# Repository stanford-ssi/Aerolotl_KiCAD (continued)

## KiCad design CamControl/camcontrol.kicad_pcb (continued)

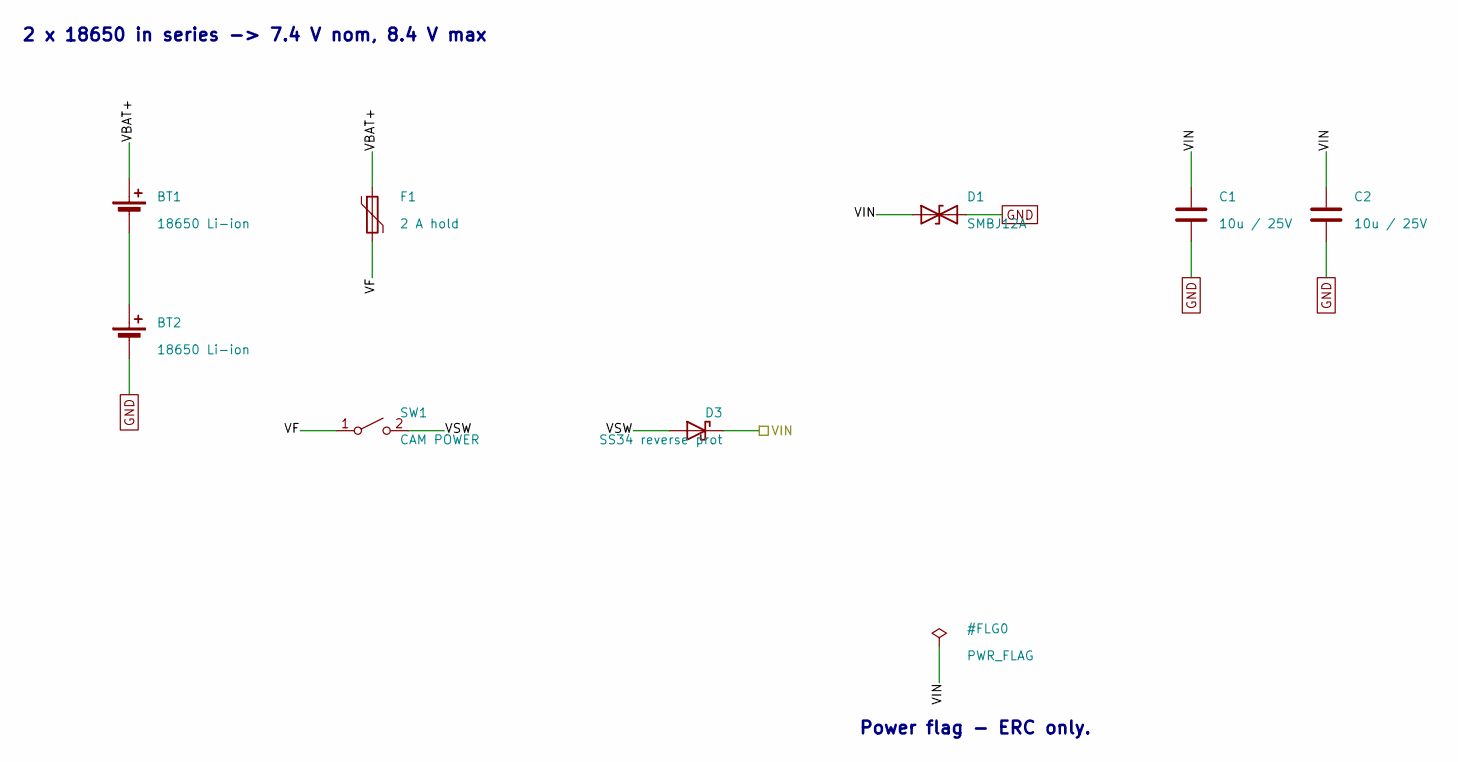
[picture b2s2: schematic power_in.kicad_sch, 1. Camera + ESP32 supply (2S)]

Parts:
BT1, BT2: 18650 Li-ion; BatteryHolder_Keystone_1042_1x18650; MPN 1042
C1, C2: 10u / 25V; C_0805_2012Metric; MPN CL21A106KAYNNNE
D1: SMBJ12A; D_SMB; MPN SMBJ12A
D3: SS34 reverse prot; D_SMB; MPN B340B-13-F
F1: 2 A hold; Fuse_1812_4532Metric; MPN 1812L200/12DR
SW1: CAM POWER; Molex_Micro-Fit_3.0_43650-0215_1x02_P3.00mm_Vertical; MPN 0436500215

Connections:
/1. Battery 2S + protection/VBAT+: BT1.1 (+), F1.1
/1. Battery 2S + protection/VF: F1.2, SW1.1 (A)
/1. Battery 2S + protection/VIN: C1.1, C2.1, D1.1 (A1), D3.1 (K); also elsewhere on the board
/1. Battery 2S + protection/VSW: D3.2 (A), SW1.2 (B)
GND: BT2.2 (-), C1.2, C2.2, D1.2 (A2); also elsewhere on the board
unnamed: BT1.2 (-), BT2.1 (+)

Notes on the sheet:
2 x 18650 in series -> 7.4 V nom, 8.4 V max
Power flag - ERC only.

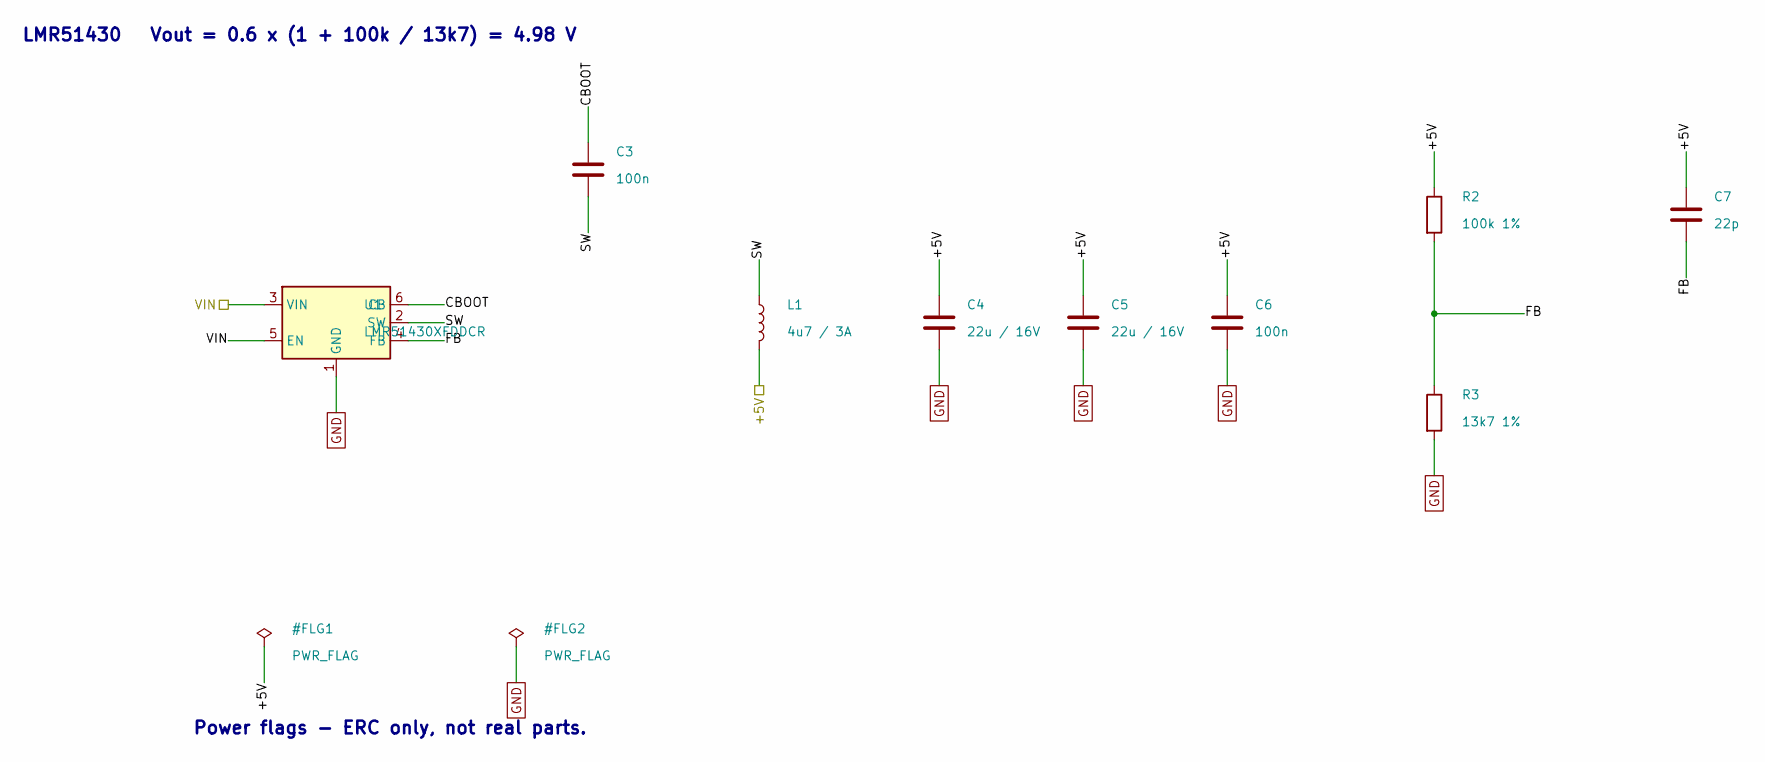
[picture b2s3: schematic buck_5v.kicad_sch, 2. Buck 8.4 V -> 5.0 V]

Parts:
C3, C6: 100n; C_0603_1608Metric; MPN CL10B104KB8NNNC
C4, C5: 22u / 16V; C_0805_2012Metric; MPN CL21A226MOQNNNE
C7: 22p; C_0603_1608Metric; MPN CL10C220JB8NNNC
L1: 4u7 / 3A; L_Bourns_SRN6045TA; MPN SRN6045TA-4R7M
R2: 100k 1%; R_0603_1608Metric; MPN RC0603FR-07100KL
R3: 13k7 1%; R_0603_1608Metric; MPN RC0603FR-0713K7L
U1: LMR51430XFDDCR; SOT-23-6; MPN LMR51430XFDDCR

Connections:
/1. Battery 2S + protection/VIN: U1.3 (VIN), U1.5 (EN); also elsewhere on the board
/2. Buck to 5 V/+5V: C4.1, C5.1, C6.1, C7.1, L1.2, R2.1; also elsewhere on the board
/2. Buck to 5 V/CBOOT: C3.1, U1.6 (CB)
/2. Buck to 5 V/FB: C7.2, R2.2, R3.1, U1.4 (FB)
/2. Buck to 5 V/SW: C3.2, L1.1, U1.2 (SW)
GND: C4.2, C5.2, C6.2, R3.2, U1.1 (GND); also elsewhere on the board

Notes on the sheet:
LMR51430 Vout = 0.6 x (1 + 100k / 13k7) = 4.98 V
Power flags - ERC only, not real parts.

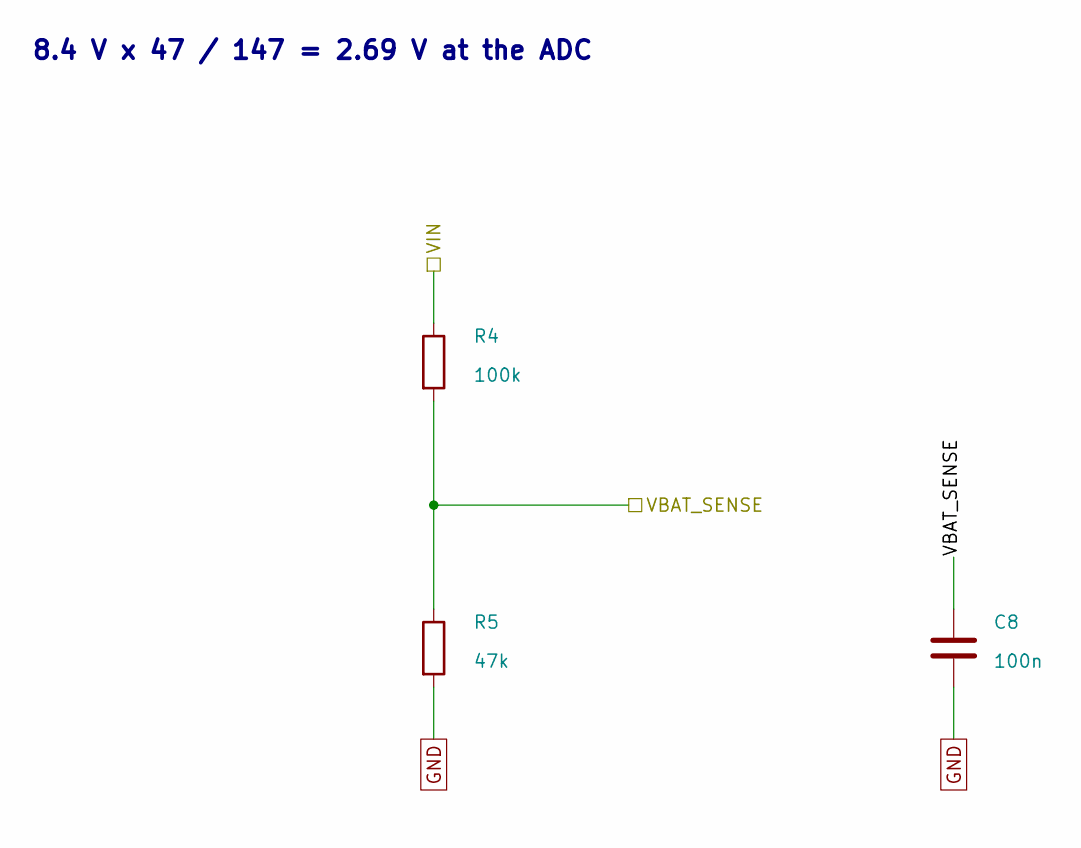
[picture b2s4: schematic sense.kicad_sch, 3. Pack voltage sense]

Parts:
C8: 100n; C_0603_1608Metric; MPN CL10B104KB8NNNC
R4: 100k; R_0603_1608Metric; MPN RC0603FR-07100KL
R5: 47k; R_0603_1608Metric; MPN RC0603FR-0747KL

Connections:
/1. Battery 2S + protection/VIN: R4.1; also elsewhere on the board
/3. Pack voltage sense/VBAT_SENSE: C8.1, R4.2, R5.1; also elsewhere on the board
GND: C8.2, R5.2; also elsewhere on the board

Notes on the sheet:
8.4 V x 47 / 147 = 2.69 V at the ADC

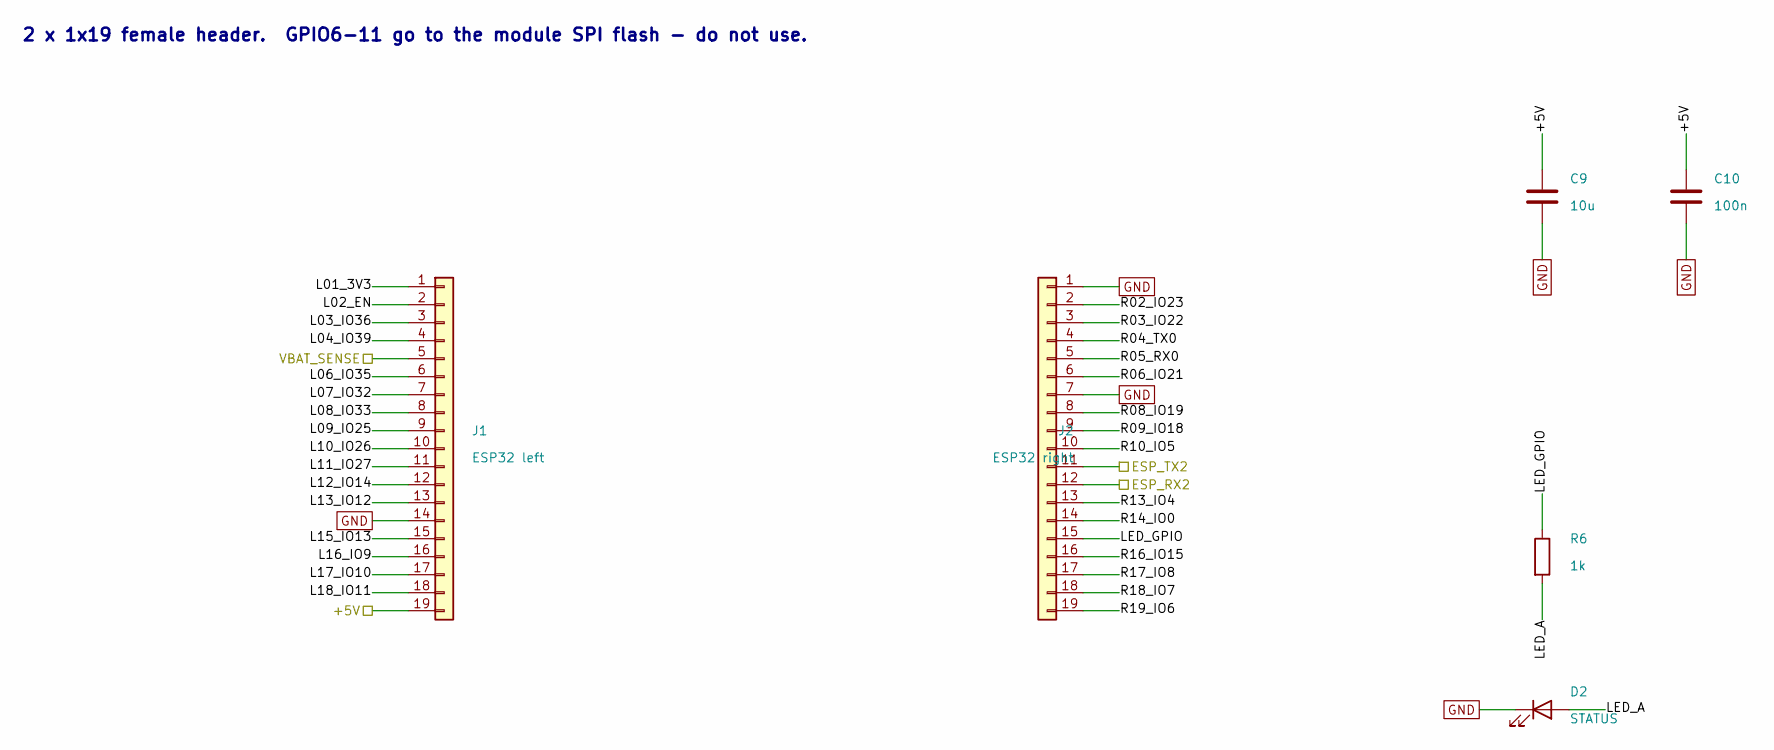
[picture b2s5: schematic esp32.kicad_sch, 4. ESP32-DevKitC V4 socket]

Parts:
C9: 10u; C_0805_2012Metric; MPN CL21A106KAYNNNE
C10: 100n; C_0603_1608Metric; MPN CL10B104KB8NNNC
D2: STATUS; LED_0805_2012Metric; MPN LTST-C171KRKT
J1: ESP32 left; PinSocket_1x19_P2.54mm_Vertical; MPN PPTC191LFBN-RC
J2: ESP32 right; PinSocket_1x19_P2.54mm_Vertical; MPN PPTC191LFBN-RC
R6: 1k; R_0603_1608Metric; MPN RC0603FR-071KL

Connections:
/2. Buck to 5 V/+5V: C9.1, C10.1, J1.19; also elsewhere on the board
/3. Pack voltage sense/VBAT_SENSE: J1.5; also elsewhere on the board
/4. ESP32 socket/ESP_RX2: J2.12; also elsewhere on the board
/4. ESP32 socket/ESP_TX2: J2.11; also elsewhere on the board
/4. ESP32 socket/L01_3V3: J1.1
/4. ESP32 socket/L02_EN: J1.2
/4. ESP32 socket/L03_IO36: J1.3
/4. ESP32 socket/L04_IO39: J1.4
/4. ESP32 socket/L06_IO35: J1.6
/4. ESP32 socket/L07_IO32: J1.7
/4. ESP32 socket/L08_IO33: J1.8
/4. ESP32 socket/L09_IO25: J1.9
/4. ESP32 socket/L10_IO26: J1.10
/4. ESP32 socket/L11_IO27: J1.11
/4. ESP32 socket/L12_IO14: J1.12
/4. ESP32 socket/L13_IO12: J1.13
/4. ESP32 socket/L15_IO13: J1.15
/4. ESP32 socket/L16_IO9: J1.16
/4. ESP32 socket/L17_IO10: J1.17
/4. ESP32 socket/L18_IO11: J1.18
/4. ESP32 socket/LED_A: D2.2 (A), R6.2
/4. ESP32 socket/LED_GPIO: J2.15, R6.1
/4. ESP32 socket/R02_IO23: J2.2
/4. ESP32 socket/R03_IO22: J2.3
/4. ESP32 socket/R04_TX0: J2.4
/4. ESP32 socket/R05_RX0: J2.5
/4. ESP32 socket/R06_IO21: J2.6
/4. ESP32 socket/R08_IO19: J2.8
/4. ESP32 socket/R09_IO18: J2.9
/4. ESP32 socket/R10_IO5: J2.10
/4. ESP32 socket/R13_IO4: J2.13
/4. ESP32 socket/R14_IO0: J2.14
/4. ESP32 socket/R16_IO15: J2.16
/4. ESP32 socket/R17_IO8: J2.17
/4. ESP32 socket/R18_IO7: J2.18
/4. ESP32 socket/R19_IO6: J2.19
GND: C9.2, C10.2, D2.1 (K), J1.14, J2.1, J2.7; also elsewhere on the board

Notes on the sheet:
2 x 1x19 female header. GPIO6-11 go to the module SPI flash - do not use.

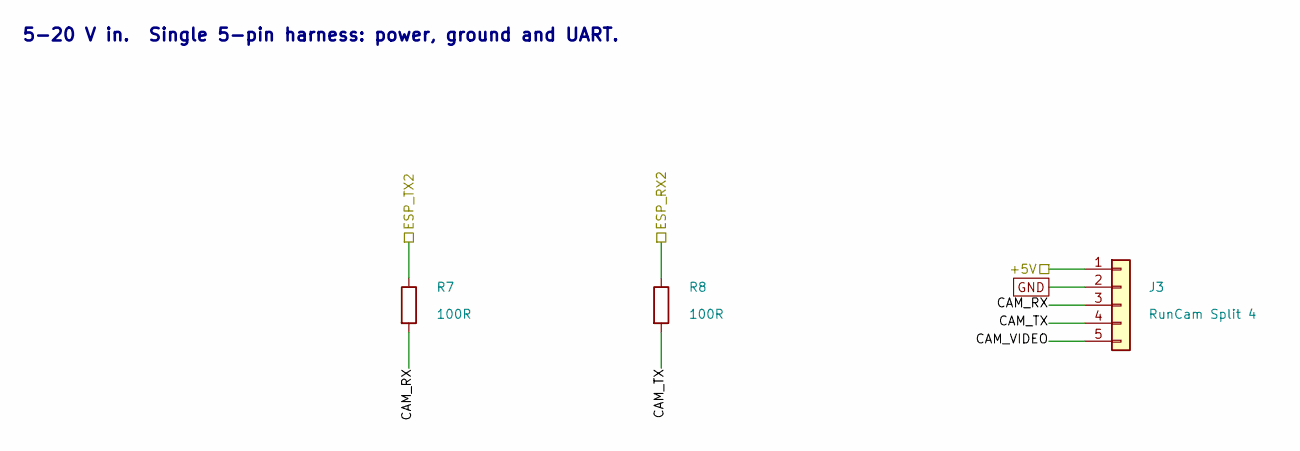
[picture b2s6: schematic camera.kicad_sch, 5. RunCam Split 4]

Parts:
J3: RunCam Split 4; JST_GH_BM05B-GHS-TBT_1x05-1MP_P1.25mm_Vertical; MPN BM05B-GHS-TBT
R7, R8: 100R; R_0603_1608Metric; MPN RC0603FR-07100RL

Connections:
/2. Buck to 5 V/+5V: J3.1; also elsewhere on the board
/4. ESP32 socket/ESP_RX2: R8.1; also elsewhere on the board
/4. ESP32 socket/ESP_TX2: R7.1; also elsewhere on the board
/5. RunCam Split 4/CAM_RX: J3.3, R7.2
/5. RunCam Split 4/CAM_TX: J3.4, R8.2
/5. RunCam Split 4/CAM_VIDEO: J3.5
GND: J3.2; also elsewhere on the board

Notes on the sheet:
5-20 V in. Single 5-pin harness: power, ground and UART.

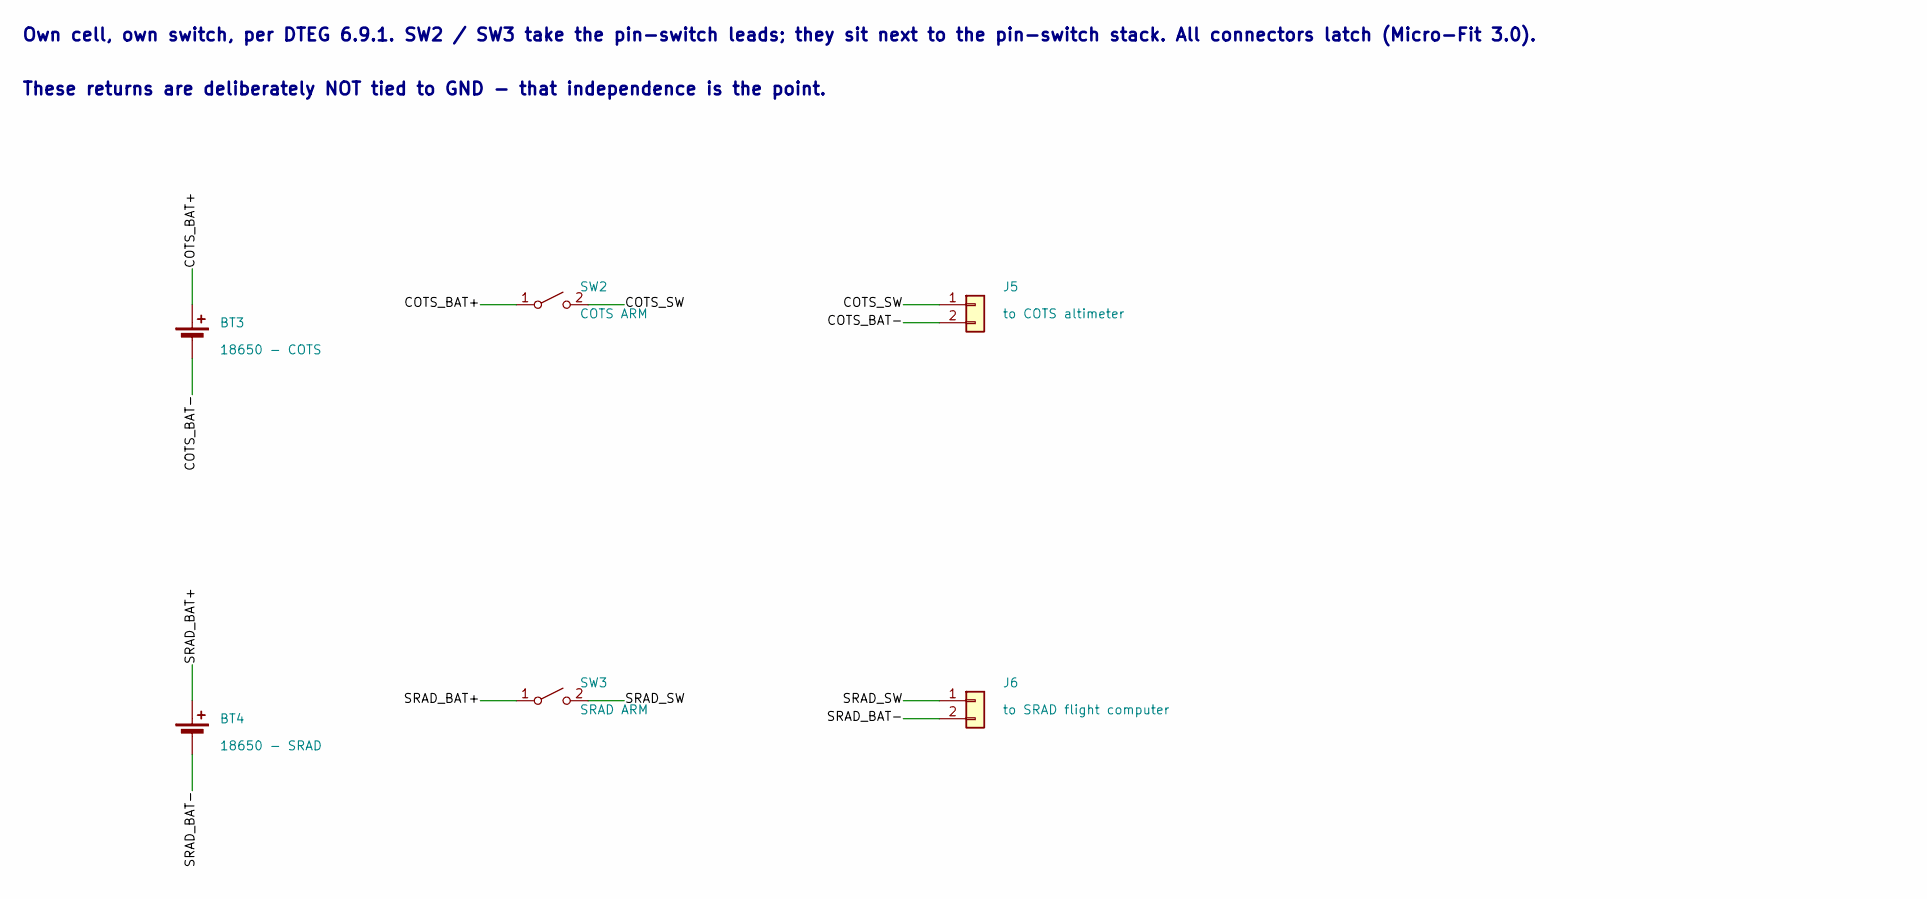
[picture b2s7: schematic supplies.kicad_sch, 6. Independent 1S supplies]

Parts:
BT3: 18650 - COTS; BatteryHolder_Keystone_1042_1x18650; MPN 1042
BT4: 18650 - SRAD; BatteryHolder_Keystone_1042_1x18650; MPN 1042
J5: to COTS altimeter; Molex_Micro-Fit_3.0_43650-0215_1x02_P3.00mm_Vertical; MPN 0436500215
J6: to SRAD flight computer; JST_XH_B2B-XH-A_1x02_P2.50mm_Vertical; MPN B2B-XH-A(LF)(SN)
SW2: COTS ARM; Molex_Micro-Fit_3.0_43650-0215_1x02_P3.00mm_Vertical; MPN 0436500215
SW3: SRAD ARM; Molex_Micro-Fit_3.0_43650-0215_1x02_P3.00mm_Vertical; MPN 0436500215

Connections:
/6. COTS / SRAD supplies/COTS_BAT+: BT3.1 (+), SW2.1 (A)
/6. COTS / SRAD supplies/COTS_BAT-: BT3.2 (-), J5.2
/6. COTS / SRAD supplies/COTS_SW: J5.1, SW2.2 (B)
/6. COTS / SRAD supplies/SRAD_BAT+: BT4.1 (+), SW3.1 (A)
/6. COTS / SRAD supplies/SRAD_BAT-: BT4.2 (-), J6.2
/6. COTS / SRAD supplies/SRAD_SW: J6.1, SW3.2 (B)

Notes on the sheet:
Own cell, own switch, per DTEG 6.9.1. SW2 / SW3 take the pin-switch leads; they sit next to the pin-switch stack. All connectors latch (Micro-Fit 3.0).
These returns are deliberately NOT tied to GND - that independence is the point.

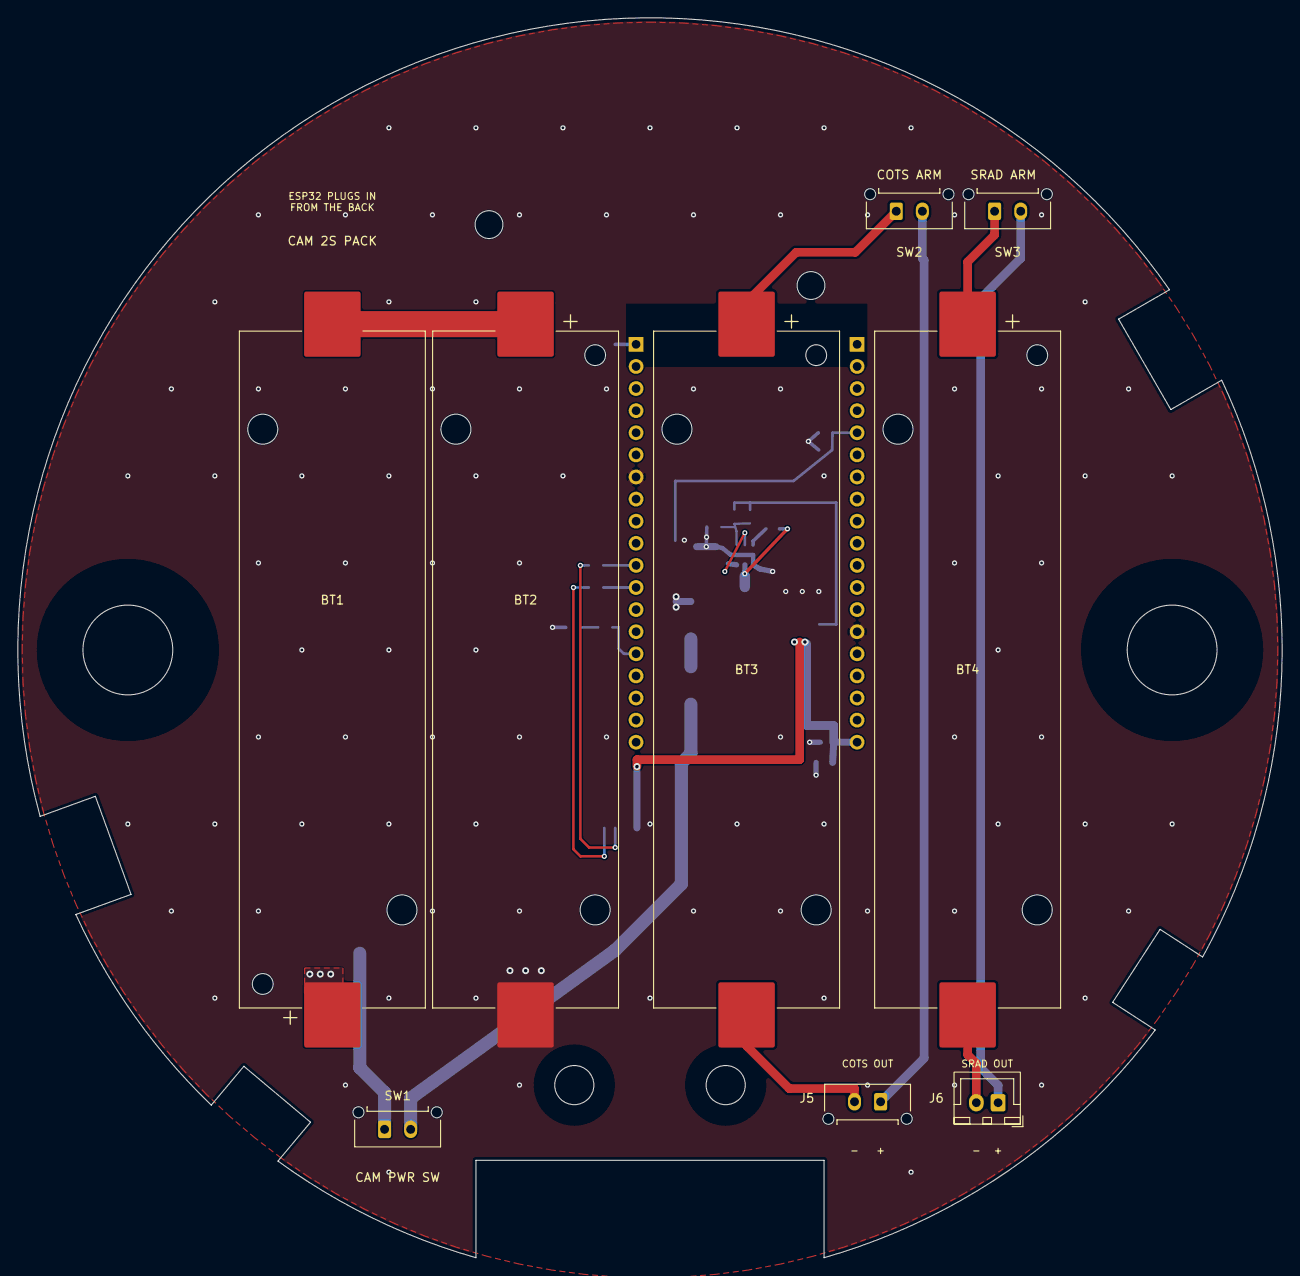
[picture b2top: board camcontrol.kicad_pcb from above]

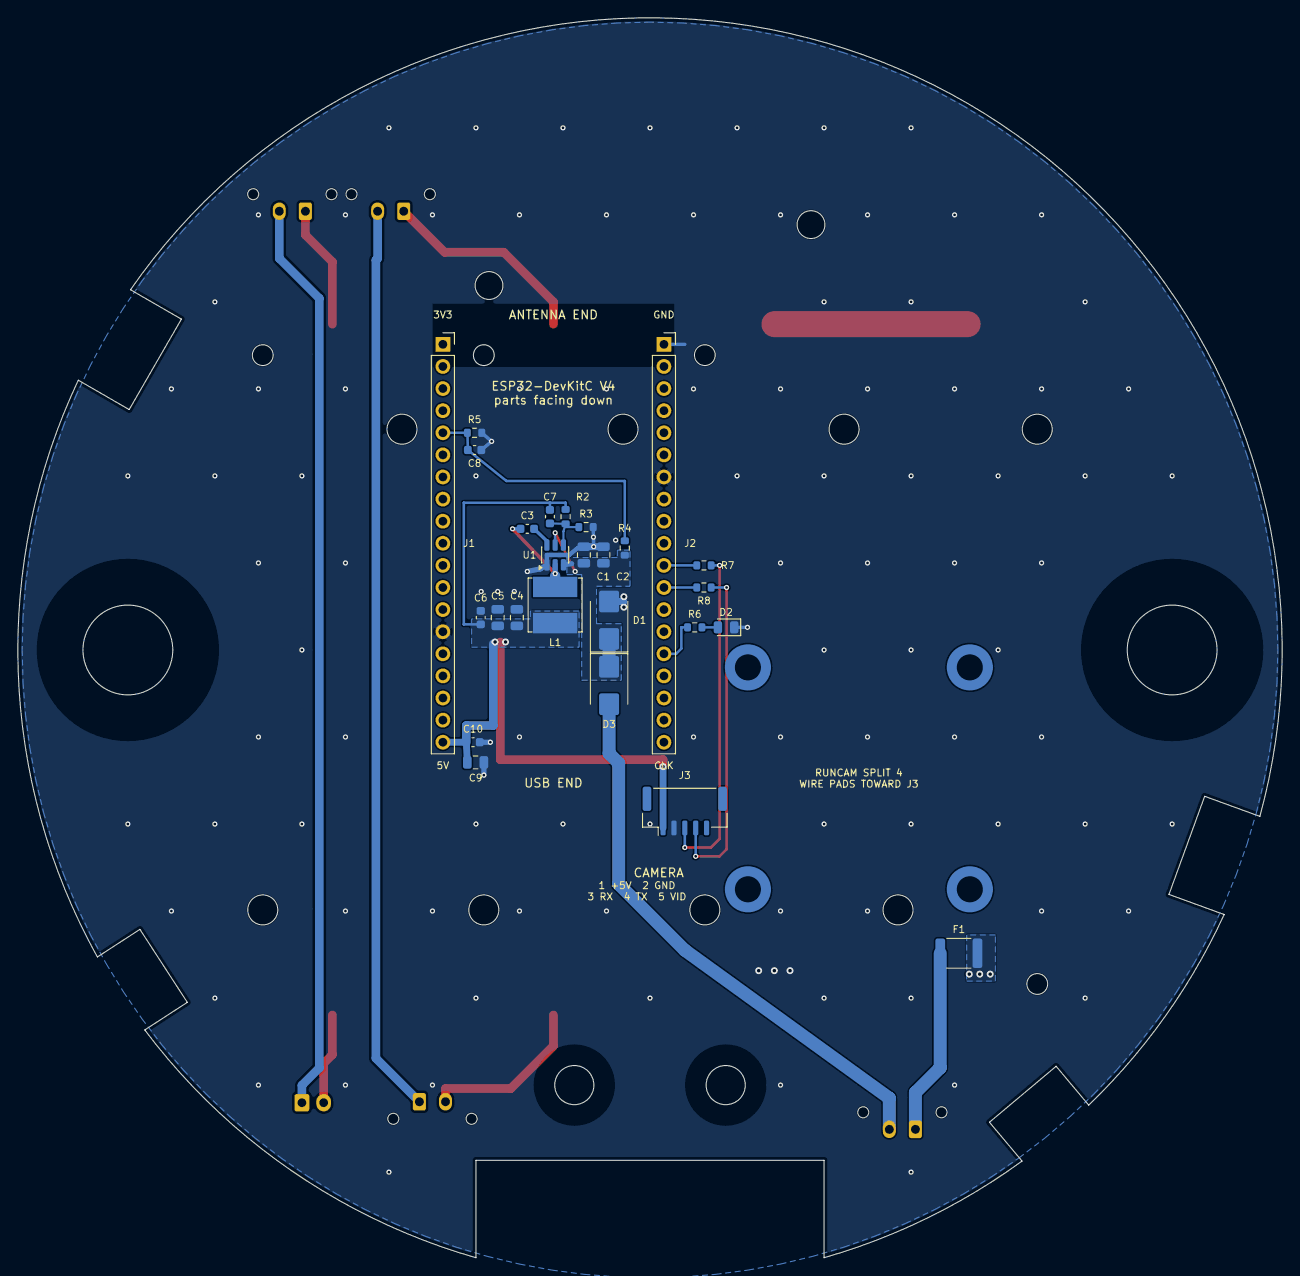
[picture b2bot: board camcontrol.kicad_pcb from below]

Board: 2 copper layers, 145.3 x 142.5 mm, 46 parts (31 on the bottom side), 23 nets.

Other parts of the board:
CAM1: RunCam Split 4 (on standoffs); RunCam_Split4_OnStandoffs
H1, H2: 3/8 rod; MountingHole_10.3mm_3-8in_Rod
H3: TeleMetrum sled M4; MountingHole_4.5mm_TeleMetrum_Sled_L
H4: TeleMetrum sled M4; MountingHole_4.5mm_TeleMetrum_Sled_R
H5, H6: Pin switch stack M3; MountingHole_3.2mm_M3_RoundStandoff_D5
H7, H8, H9, H10: Wurth 9774050243 M2x5 standoff (camera); Mounting_Wuerth_WA-SMSI-M2_H5mm_9774050243_NoHole

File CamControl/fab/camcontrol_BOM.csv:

Section,Qty per board,Order qty (2 boards + spares),References,Description,Manufacturer,MPN,Footprint,Notes
Board (solder on),4,8,"BT1, BT2, BT3, BT4","Battery holder, 1x 18650, surface mount",Keystone Electronics,1042,BatteryHolder_Keystone_1042_1x18650,
Board (solder on),3,11,"C1, C2, C9","Capacitor 10 uF 25 V X5R, 0805",Samsung Electro-Mechanics,CL21A106KAYNNNE,C_0805_2012Metric,
Board (solder on),4,13,"C3, C6, C8, C10","Capacitor 100 nF 50 V X7R, 0603",Samsung Electro-Mechanics,CL10B104KB8NNNC,C_0603_1608Metric,
Board (solder on),2,10,"C4, C5","Capacitor 22 uF 16 V X5R, 0805",Samsung Electro-Mechanics,CL21A226MOQNNNE,C_0805_2012Metric,
Board (solder on),1,10,C7,"Capacitor 22 pF 50 V C0G, 0603",Samsung Electro-Mechanics,CL10C220JB8NNNC,C_0603_1608Metric,
Board (solder on),1,3,D1,"TVS diode, 12 V standoff, SMB",Littelfuse,SMBJ12A,D_SMB,
Board (solder on),1,10,D2,"LED, red, 0805 (status light)",Lite-On,LTST-C171KRKT,LED_0805_2012Metric,
Board (solder on),1,3,D3,"Schottky diode 40 V 3 A, SMB (reverse-polarity protection)",Diodes Incorporated,B340B-13-F,D_SMB,
Board (solder on),1,3,F1,"Resettable fuse (PTC) 2 A hold, 12 V, 1812",Littelfuse,1812L200/12DR,Fuse_1812_4532Metric,Alt: Polytronics SMD1812P200TF/16
Board (solder on),2,5,"J1, J2","Female header 1x19, 2.54 mm (socket for the ESP32-DevKitC)",Sullins Connector Solutions,PPTC191LFBN-RC,PinSocket_1x19_P2.54mm_Vertical,
Board (solder on),1,3,J3,JST GH 5-pin vertical header (camera),JST,BM05B-GHS-TBT,JST_GH_BM05B-GHS-TBT_1x05-1MP_P1.25mm_Vertical,
Board (solder on),4,9,"J5, SW1, SW2, SW3",Molex Micro-Fit 3.0 2-pin vertical header,Molex,0436500215,Molex_Micro-Fit_3.0_43650-0215_1x02_P3.00mm_Vertical,"SW1 camera power, SW2/SW3 pin-switch leads, J5 to the TeleMetrum"
Board (solder on),1,3,J6,JST XH 2-pin vertical header (to the Aerolotl),JST,B2B-XH-A(LF)(SN),JST_XH_B2B-XH-A_1x02_P2.50mm_Vertical,"Friction fit, not latching"
Board (solder on),1,3,L1,"Power inductor 4.7 uH 4.5 A, 6 x 6 mm",Bourns,SRN6045TA-4R7M,L_Bourns_SRN6045TA,
Board (solder on),2,10,"R2, R4","Resistor 100 k 1%, 0603",Yageo,RC0603FR-07100KL,R_0603_1608Metric,
Board (solder on),1,10,R3,"Resistor 13.7 k 1%, 0603",Yageo,RC0603FR-0713K7L,R_0603_1608Metric,
Board (solder on),1,10,R5,"Resistor 47 k 1%, 0603",Yageo,RC0603FR-0747KL,R_0603_1608Metric,
Board (solder on),1,10,R6,"Resistor 1 k 1%, 0603",Yageo,RC0603FR-071KL,R_0603_1608Metric,
Board (solder on),2,10,"R7, R8","Resistor 100 ohm 1%, 0603",Yageo,RC0603FR-07100RL,R_0603_1608Metric,
Board (solder on),1,3,U1,"Buck converter 4.5-36 V in, 3 A, SOT-23-6 (makes the 5 V rail)",Texas Instruments,LMR51430XFDDCR,SOT-23-6,
Board hardware,4,8,H7-H10,"SMT steel standoff, M2 thread, 5 mm (camera mounts, back side)",Wurth Elektronik,9774050243,,Soldered like a part
Plugs in / mounts on,1,2,,"ESP32 dev board, DevKitC V4",Espressif,ESP32-DevKitC-32E,,Plugs into J1/J2 from the back
Plugs in / mounts on,1,2,,"Camera, RunCam Split 4",RunCam,Split 4,,Sits on H7-H10; check its cable ends in a JST GH 5-pin for J3
Plugs in / mounts on,4,8,,"Screw M2 x 4 mm, pan head",,,,Camera to standoffs
Plugs in / mounts on,4,8,,"18650 Li-ion cell, flat top, high drain",Molicel,INR-18650-P28A,,Or any high-drain flat-top 18650; never mix cells in the series pair
Cable side,4,8,"SW1, SW2, SW3, J5","Micro-Fit 3.0 receptacle housing, 2-pin",Molex,0436450200,,
Cable side,8,16,"SW1, SW2, SW3, J5","Micro-Fit 3.0 female crimp terminal, 20-24 AWG",Molex,0430300007,,"Needs a Micro-Fit crimper, or buy pre-crimped leads"
Cable side,1,2,J6,"JST XH housing, 2-pin",JST,XHP-2,,
Cable side,2,4,J6,"JST XH crimp terminal, 22-28 AWG",JST,SXH-001T-P0.6,,
Cable side,1,2,J3,"JST GH housing, 5-pin",JST,GHR-05V-S,,Or a pre-crimped GH 5-pin cable
Cable side,5,10,J3,"JST GH crimp terminal, 26-30 AWG",JST,SSHL-002T-P0.2,,
Cable side,1,2,SW1,"Toggle switch, SPST, 3 A or more, panel mount",,,,"Camera power switch, wired to the SW1 plug"
PCB,1,5,,"PCB, 2 layers, 145.3 mm (5.72 in) round, 1.6 mm FR-4, 1 oz copper",JLCPCB (or any fab),,,Upload fab/camcontrol_gerbers.zip; 5 is the usual minimum order

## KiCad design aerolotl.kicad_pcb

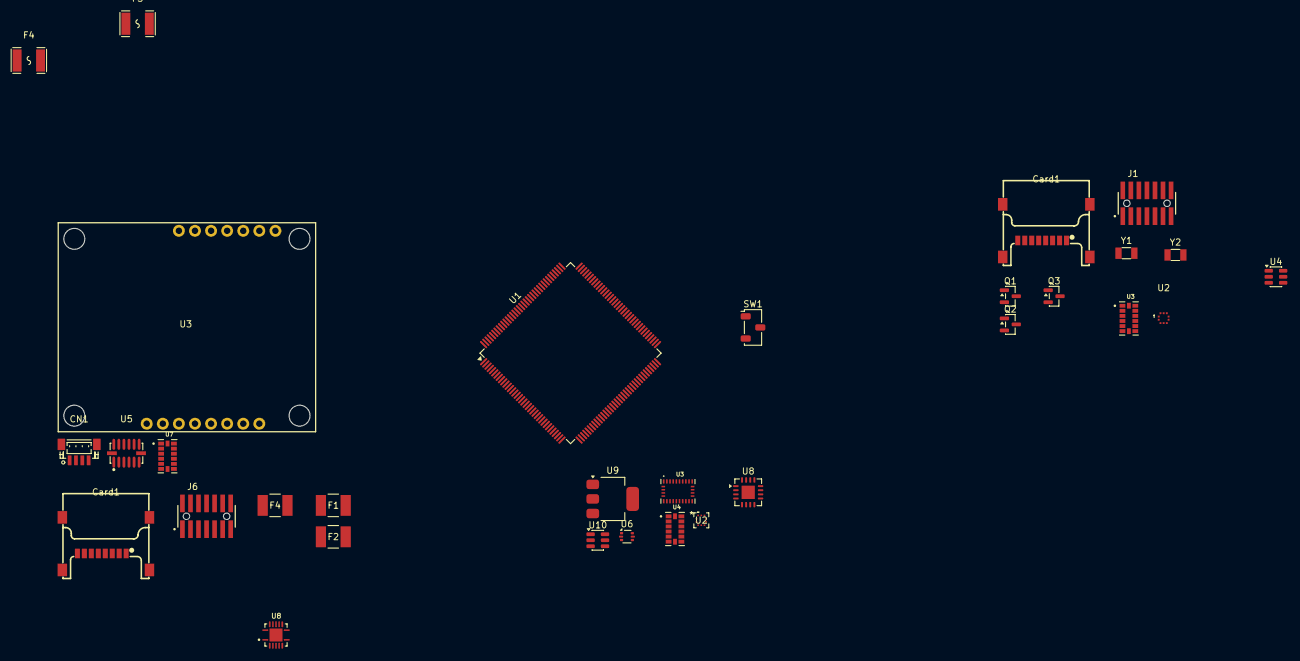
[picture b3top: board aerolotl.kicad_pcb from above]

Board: 2 copper layers, 31 parts (0 on the bottom side), 33 nets, no tracks yet.

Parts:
CN1: StemmaQT; CONN-SMD_BM04B-SRSS-TB
Card1: TF-102-15_SD_read; TF-SMD_TF-102-15
Card1#2: TF-102-15; TF-SMD_TF-102-15
F1, F2, F4#2: 1812L150/24MR; FUSE_1812L150&slash_24_LTF
F3, F4: 1812L300/24SLER; F1812
J1: SWD; SAMTEC_FTSH-107-01-L-DV-K-A
J6: FTSH-107-STDC14; SAMTEC_FTSH-107-01-L-DV-K-A
Q1, Q2, Q3: AO3400A; SOT-23
SW1: SW_Nidec_CAS-120A1; Nidec_Copal_CAS-120A
U1: STM32H755ZIT6; LQFP-144_20x20mm_P0.5mm
U2: BMP581; LGA-10_L2.0-W2.0-P0.50-TL_BMP581
U2#2: BMP581; QFN10_BMP581_BOS
U3: BNO085; IC_BNO085
U3#2, U4#2: ADXL345BCCZ-RL7; PQFN80P500X300X100-14N
U3#3: SparkfunM9N
U4, U10: LMR51430XFDDCR; SOT-23-6
U5: ADXL375BCCZ-RL7; LGA-14_L5.0-W3.0-P0.80-BL
U6: USBLC6-2P6; SOT-666
U7: ADXL345BCCZ-RL7; ADXL345
U8: TPS54620RGYR; TPS54620_7v4buck
U8#2: FT230XQ; QFN-16-1EP_4x4mm_P0.65mm_EP2.1x2.1mm
U9: AMS1117-3.3; SOT-223-3_TabPin2
Y1: 25M; Crystal_SMD_3215-2Pin_3.2x1.5mm
Y2: 32k768; Crystal_SMD_3215-2Pin_3.2x1.5mm

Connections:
+3V3: Card1.4 (VDD), Card1#2.4 (VDD), J6.03, SW1.3 (A), U1.7 (VDD), U1.8 (VBAT), U1.13 (VDD), U1.16 (VDDSMPS), U1.19 (VDD), U1.32 (VDD), U1.42 (VDD), U1.56 (VDD), U1.70 (VDDLDO), U1.71 (VDD), U1.79 (VDD), U1.90 (VDD50_USB), U1.91 (VDD33_USB), U1.92 (VDD), U1.105 (VDDLDO), U1.106 (VDD), U1.119 (VDD), U1.129 (VDD), U1.142 (PDR_ON), U1.143 (VDDLDO), U1.144 (VDD), U3#3.6 (3V3), U3#3.11 (3V3)
+7V4_SERVO: F3.1, F4.1
+12V: U4.3 (VIN), U4.5 (EN)
+12V_ARM: F1.2, F2.2
/Debugger/T_SWCLK: J1.06, J6.06, U1.107 (PA14)
/Debugger/T_SWDIO: J1.04, J6.04, U1.102 (PA13)
/Debugger/T_SWO: J1.08, J6.08, U1.130 (PB3)
/Debugger/T_VCP_RX: J1.14, J6.14, U1.98 (PA9)
/Debugger/T_VCP_TX: J1.13, J6.13, U1.99 (PA10)
/IMUs/ADXL345.CS: U3#2.7 (~CS), U7.7 (~CS)
/IMUs/ADXL345.SCLK: U1.44 (PA5), U2.2 (SCK), U3#2.14 (SCL/SCLK), U5.14 (SCL/SCLK), U7.14 (SCL/SCLK)
/IMUs/ADXL345.SDI: U1.45 (PA6), U2.5 (SDO), U3#2.13 (SDA/SDI/SDIO), U5.12 (SDO/ALTADDRESS), U7.13 (SDA/SDI/SDIO)
/IMUs/ADXL345.SDO: U1.46 (PA7), U2.4 (SDI), U3#2.12 (SDO/ALT_ADDRESS), U5.13 (SDA/SDI/SDIO), U7.12 (SDO/ALT_ADDRESS)
/MCU/BOOT0: SW1.2 (B), U1.135 (BOOT0)
/MCU/HS_OSC_A: U1.25 (PH0), Y1.1
/MCU/HS_OSC_B: U1.26 (PH1), Y1.2
/MCU/LS_OSC_A: U1.10 (PC14), Y2.2
/MCU/LS_OSC_B: U1.11 (PC15), Y2.1
/MCU/RESET: J6.12, U1.27 (NRST)
/MCU/SDMMC1.CK: Card1.5 (CLK), Card1#2.5 (CLK), U1.111 (PC12)
/MCU/SDMMC1.CMD: Card1.3 (CMD), Card1#2.3 (CMD), U1.114 (PD2)
/MCU/SDMMC1.D0: Card1.7 (DAT0), Card1#2.7 (DAT0), U1.95 (PC8)
/MCU/SDMMC1.D1: Card1.8 (DAT1), Card1#2.8 (DAT1), U1.96 (PC9)
/MCU/SDMMC1.D2: Card1.1 (DAT2), Card1#2.1 (DAT2), U1.109 (PC10)
/MCU/SDMMC1.D3: Card1.2 (CD/DAT3), Card1#2.2 (CD/DAT3), U1.110 (PC11)
/MCU/USB_D_M: U1.100 (PA11), U6.6 (I/O1)
/MCU/USB_D_P: U1.101 (PA12), U6.4 (I/O2)
/MCU/VFBSMPS: U1.17 (VFBSMPS), U1.68 (VCAP), U1.103 (VCAP), U1.140 (VCAP)
/Power/P_VBUS: U6.5 (VBUS), U9.3 (VI)
/USB to UART/VCCIO: U8#2.1 (VCCIO), U8#2.8 (3V3OUT), U8#2.9 (~RESET)
GND: CN1.0, CN1.1, Card1.6 (VSS), Card1.9 (SHELL), Card1.10 (SHELL), Card1.11 (SHELL), Card1.12 (SHELL), Card1#2.6 (VSS), Card1#2.9 (SHELL), Card1#2.10 (SHELL), Card1#2.11 (SHELL), Card1#2.12 (SHELL), J1.05, J1.07, J6.05, J6.07, Q1.2 (S), Q2.2 (S), Q3.2 (S), U1.6 (VSS), U1.12 (VSS), U1.14 (VSSSMPS), U1.18 (VSS), U1.33 (VSS), U1.34 (VSSA), U1.41 (VSS), U1.55 (VSS), U1.69 (VSS), U1.80 (VSS), U1.89 (VSS), U1.104 (VSS), U1.118 (VSS), U1.128 (VSS), U1.141 (VSS), U2.3 (VSS), U2.8 (VSS), U2.9 (VSS), U3#2.2 (GND), U3#2.4 (GND), U3#2.5 (GND), U3#3.5 (GND), U3#3.9 (GND), U4.1 (GND), U4#2.2 (GND), U4#2.4 (GND), U4#2.5 (GND), U5.2 (GND), U5.4 (GND), U5.5 (GND), U5.11 (RESERVED), U6.2 (GND), U7.2 (GND), U7.4 (GND), U7.5 (GND), U7.11 (RESERVED_11), U8#2.3 (GND), U8#2.13 (GND), U8#2.17 (GND), U9.1 (GND)
VCC: CN1.2, F4#2.2
VDD: U3#2.1 (VDD_I/O), U3#2.6 (VS), U5.1 (VDDI/O), U5.3 (RESERVED), U5.6 (VS), U7.1 (VDD_I/O), U7.3 (RESERVED_3), U7.6 (VS)
